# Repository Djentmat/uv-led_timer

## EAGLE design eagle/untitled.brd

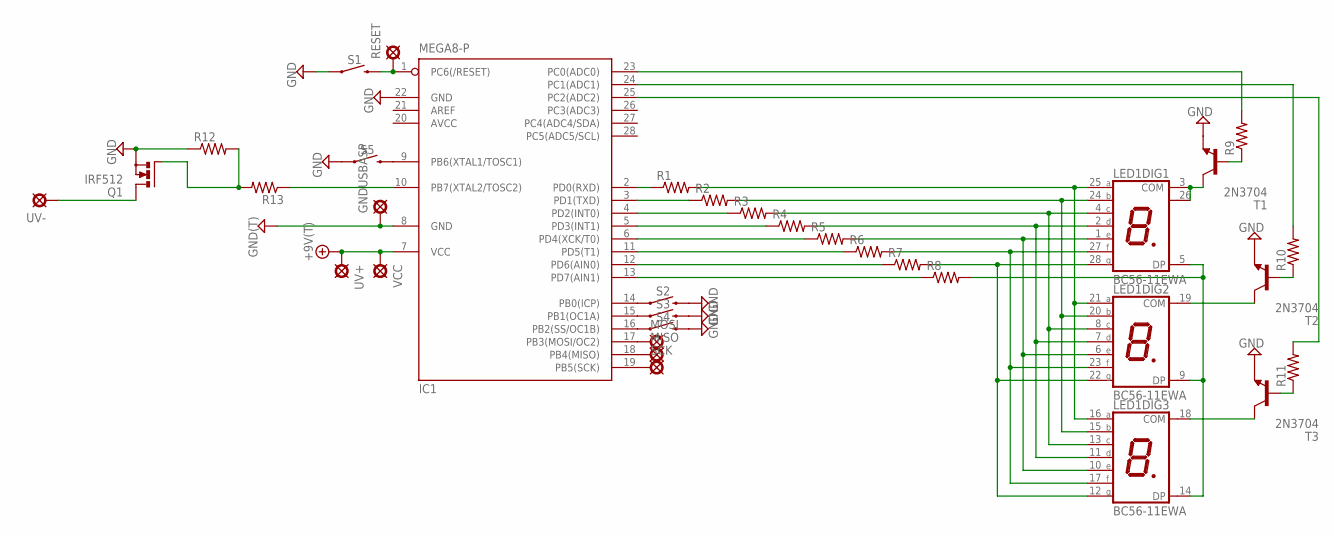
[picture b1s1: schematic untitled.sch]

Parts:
+9V1: +9V(T); SQUARE
GND1: GND(T); SQUARE
GNDUSBASP: PAD; SQUARE
IC1: MEGA8-P; DIL28-3
LED1: BC56-11EWA; BA/BC56
MISO: PAD; SQUARE
MOSI: PAD; SQUARE
Q1: IRF512; TO220BV
R1, R2, R3, R4, R5, R6, R7, R8, R9, R10, R11, R12, R13: 6MM.3; R0207/3
RESET: PAD; SQUARE
S1, S2, S3, S4, S5: MOMENTARY-SWITCH-SPST-PTH-6.0MM; TACTILE_SWITCH_PTH_6.0MM
SCK: PAD; SQUARE
T1, T2, T3: 2N3704; TO92
UV+: PAD; SQUARE
UV-: PAD; SQUARE
VCC: PAD; SQUARE

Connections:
+9V: +9V1.1, IC1.7 (VCC), UV+.1, VCC.1
AVCC: IC1.20 (AVCC)
GND: GND1.1, GNDUSBASP.1, IC1.8 (GND), IC1.22 (GND), Q1.S, R12.1, S1.1, S2.3 (2), S3.3 (2), S4.3 (2), S5.1, T1.3 (E), T2.3 (E), T3.3 (E)
unnamed: LED1.16 (A), LED1.21 (A), LED1.25 (A), R1.2
unnamed: LED1.15 (B), LED1.20 (B), LED1.24 (B), R2.2
unnamed: LED1.4 (C), LED1.8 (C), LED1.13 (C), R3.2
unnamed: LED1.2 (D), LED1.7 (D), LED1.11 (D), R4.2
unnamed: LED1.1 (E), LED1.6 (E), LED1.10 (E), R5.2
unnamed: LED1.17 (F), LED1.23 (F), LED1.27 (F), R6.2
unnamed: LED1.5 (DP), LED1.9 (DP), LED1.14 (DP), R8.2
unnamed: LED1.12 (G), LED1.22 (G), LED1.28 (G), R7.2
unnamed: LED1.3 (COM), LED1.26 (COM), T1.2 (C)
unnamed: LED1.19 (COM), T2.2 (C)
unnamed: LED1.18 (COM), T3.2 (C)
unnamed: IC1.2 (PD0(RXD)), R1.1
unnamed: IC1.3 (PD1(TXD)), R2.1
unnamed: IC1.4 (PD2(INT0)), R3.1
unnamed: IC1.5 (PD3(INT1)), R4.1
unnamed: IC1.6 (PD4(XCK/T0)), R5.1
unnamed: IC1.11 (PD5(T1)), R6.1
unnamed: IC1.12 (PD6(AIN0)), R7.1
unnamed: IC1.13 (PD7(AIN1)), R8.1
unnamed: R9.1, T1.1 (B)
unnamed: R10.1, T2.1 (B)
unnamed: R11.1, T3.1 (B)
unnamed: IC1.23 (PC0(ADC0)), R9.2
unnamed: IC1.24 (PC1(ADC1)), R10.2
unnamed: IC1.25 (PC2(ADC2)), R11.2
unnamed: IC1.1 (PC6(/RESET)), RESET.1, S1.3 (2)
unnamed: IC1.14 (PB0(ICP)), S2.1
unnamed: IC1.15 (PB1(OC1A)), S3.1
unnamed: IC1.16 (PB2(SS/OC1B)), S4.1
unnamed: IC1.9 (PB6(XTAL1/TOSC1)), S5.3 (2)
unnamed: IC1.17 (PB3(MOSI/OC2)), MOSI.1
unnamed: IC1.18 (PB4(MISO)), MISO.1
unnamed: IC1.19 (PB5(SCK)), SCK.1
unnamed: IC1.10 (PB7(XTAL2/TOSC2)), R13.1
unnamed: Q1.G, R12.2, R13.2
unnamed: Q1.D, UV-.1

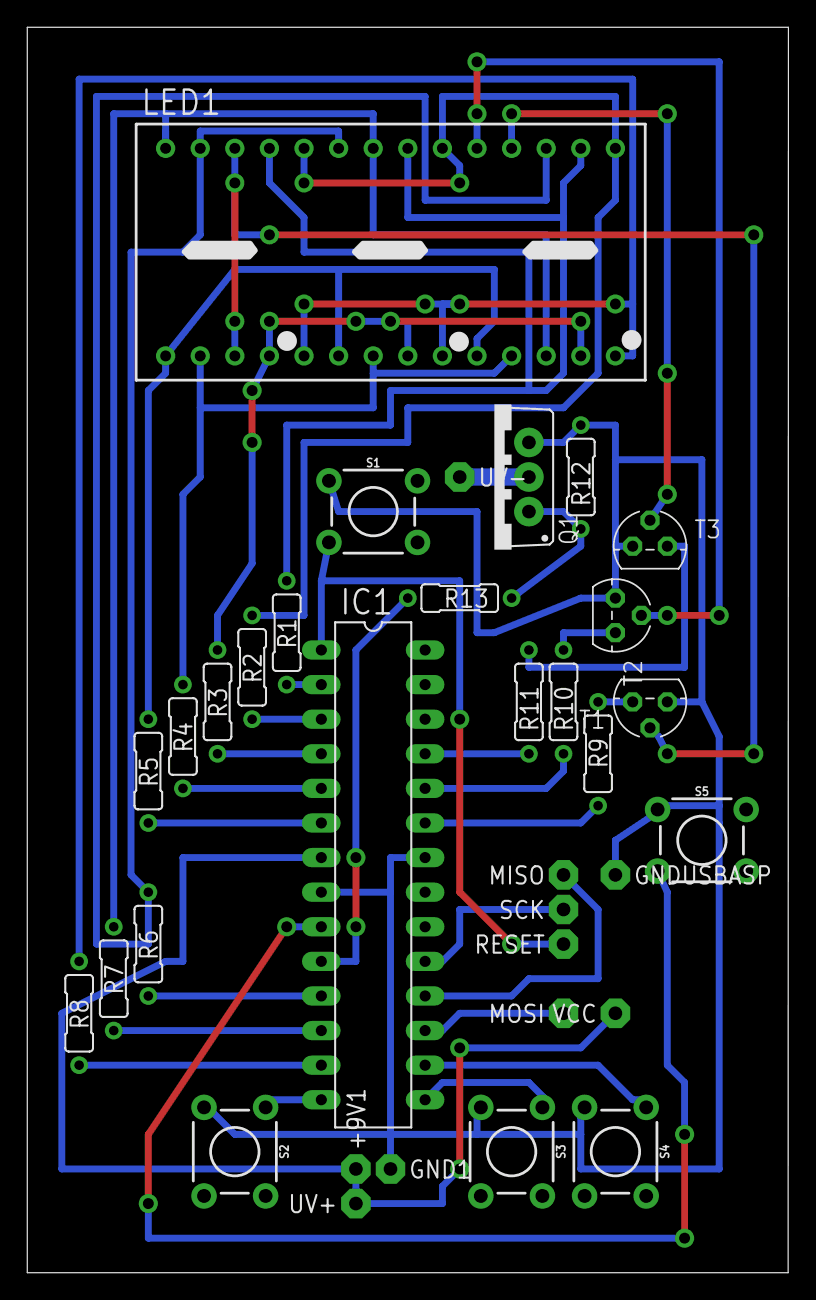
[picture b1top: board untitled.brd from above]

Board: 2 copper layers, 55.9 x 91.4 mm, 34 parts (0 on the bottom side), 38 nets.

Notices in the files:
parts and their libraries:
SparkFun-Switches: Licensing: Creative Commons ShareAlike 4.0 International - https://creativecommons.org/licenses/by-sa/4.0
